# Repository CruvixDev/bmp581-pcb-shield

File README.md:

# BMP581 shield project (Kicad)

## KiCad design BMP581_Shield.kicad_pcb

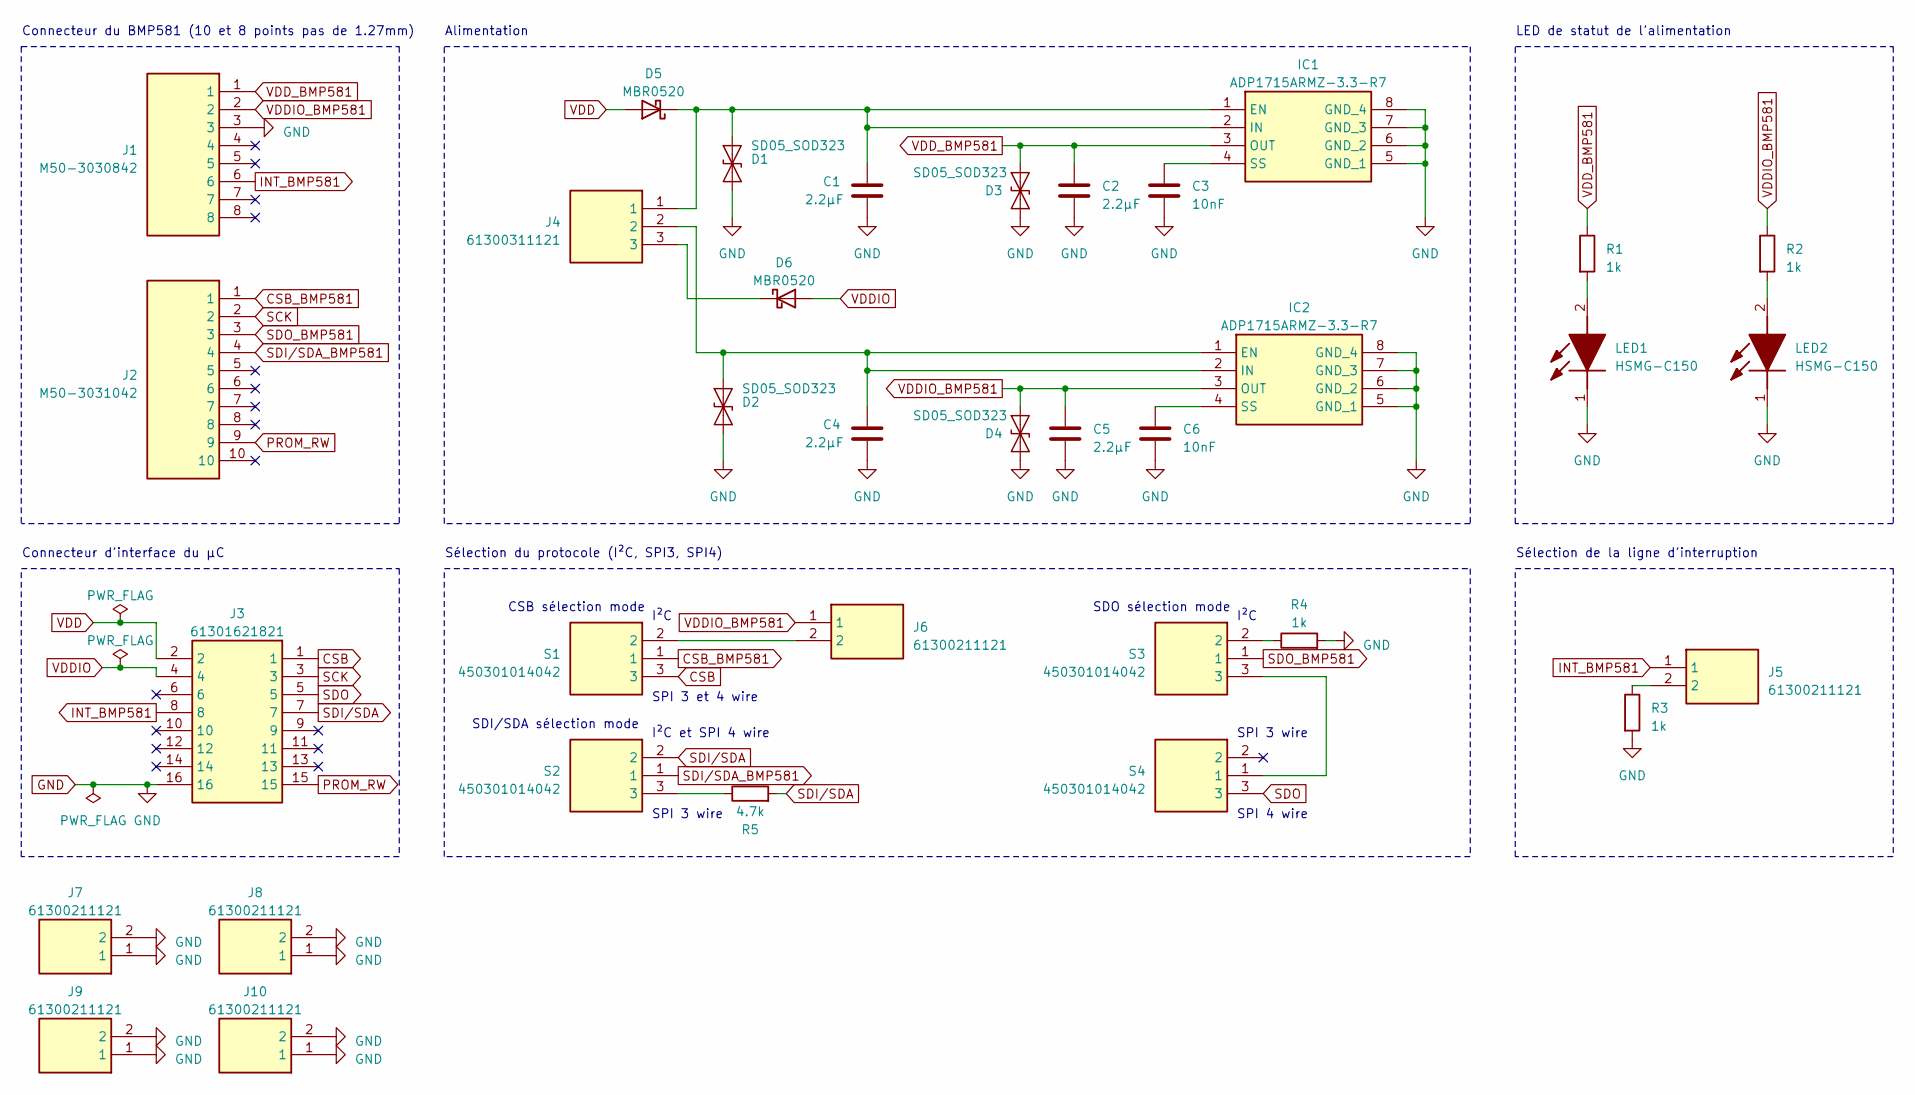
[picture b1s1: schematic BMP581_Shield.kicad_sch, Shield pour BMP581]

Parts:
C1, C2, C4, C5: 2.2µF; C_0603_1608Metric_Pad1.08x0.95mm_HandSolder
C3, C6: 10nF; C_0603_1608Metric_Pad1.08x0.95mm_HandSolder
D1, D2, D3, D4: SD05_SOD323; D_SOD-323_HandSoldering
D5, D6: MBR0520; D_SOD-123
IC1, IC2: ADP1715ARMZ-3.3-R7; SOP65P490X110-8N; Mouser Part Number 584-ADP1715ARMZ3.3R7
J1: M50-3030842; M503030842; Manufacturer_Part_Number M50-3030842; Mouser Part Number 855-M50-3030842
J2: M50-3031042; M503031042; Manufacturer_Part_Number M50-3031042; Mouser Part Number 855-M50-3031042
J3: 61301621821; RHDR16W79P254X254_2X8_2082X508X860P; Mouser Part Number 710-61301621821
J4: 61300311121; HDRV3W64P0X254_1X3_762X254X869P; Mouser Part Number 710-61300311121
J5, J6, J7, J8, J9, J10: 61300211121; HDRV2W110P0X254_1X2_508X254X854P; Mouser Part Number 710-61300211121
LED1, LED2: HSMG-C150; LEDC3216X120N; Mouser Part Number 630-HSMG-C150
R1, R2, R3, R4: 1k; R_0603_1608Metric_Pad0.98x0.95mm_HandSolder
R5: 4.7k; R_0603_1608Metric_Pad0.98x0.95mm_HandSolder
S1, S2, S3, S4: 450301014042; Mouser Part Number 710-450301014042

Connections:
CSB: J3.1, S1.3
CSB_BMP581: J2.1, S1.1
GND: C1.2, C2.2, C3.2, C4.2, C5.2, C6.2, D1.1 (A1), D2.1 (A1), D3.1 (A1), D4.1 (A1), IC1.5 (GND_1), IC1.6 (GND_2), IC1.7 (GND_3), IC1.8 (GND_4), IC2.5 (GND_1), IC2.6 (GND_2), IC2.7 (GND_3), IC2.8 (GND_4), J1.3, J3.16, J7.1, J7.2, J8.1, J8.2, J9.1, J9.2, J10.1, J10.2, LED1.1 (K), LED2.1 (K), R3.2, R4.2
INT_BMP581: J1.6, J3.8, J5.1
unnamed: C1.1, D1.2 (A2), D5.1 (K), IC1.1 (EN), IC1.2 (IN), J4.1
unnamed: C4.1, D2.2 (A2), IC2.1 (EN), IC2.2 (IN), J4.2
unnamed: D6.1 (K), J4.3
unnamed: C3.1, IC1.4 (SS)
unnamed: C6.1, IC2.4 (SS)
unnamed: J5.2, R3.1
unnamed: J6.2, S1.2
unnamed: LED1.2 (A), R1.2
unnamed: LED2.2 (A), R2.2
unnamed: R4.1, S3.2
unnamed: R5.1, S2.3
unnamed: S3.3, S4.1
PROM_RW: J2.9, J3.15
SCK: J2.2, J3.3
SDI/SDA: J3.7, R5.2, S2.2
SDI/SDA_BMP581: J2.4, S2.1
SDO: J3.5, S4.3
SDO_BMP581: J2.3, S3.1
VDD: D5.2 (A), J3.2
VDDIO: D6.2 (A), J3.4
VDDIO_BMP581: C5.1, D4.2 (A2), IC2.3 (OUT), J1.2, J6.1, R2.1
VDD_BMP581: C2.1, D3.2 (A2), IC1.3 (OUT), J1.1, R1.1

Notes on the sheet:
SPI 3 wire
I²C et SPI 4 wire
Alimentation
Connecteur d'interface du µC
LED de statut de l'alimentation
SPI 4 wire
SDI/SDA sélection mode
Connecteur du BMP581 (10 et 8 points pas de 1.27mm)
I²C
SPI 3 et 4 wire
CSB sélection mode
SDO sélection mode
Sélection du protocole (I²C, SPI3, SPI4)
Sélection de la ligne d'interruption

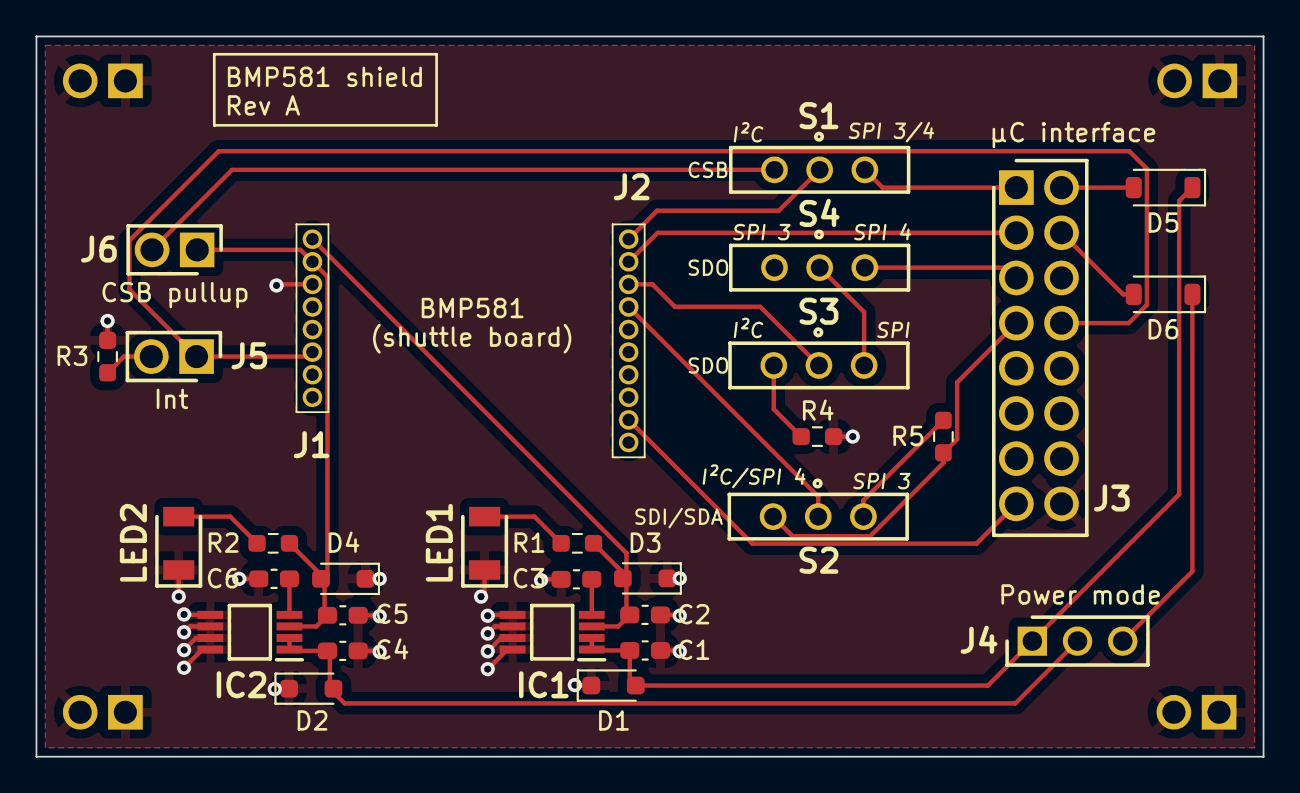
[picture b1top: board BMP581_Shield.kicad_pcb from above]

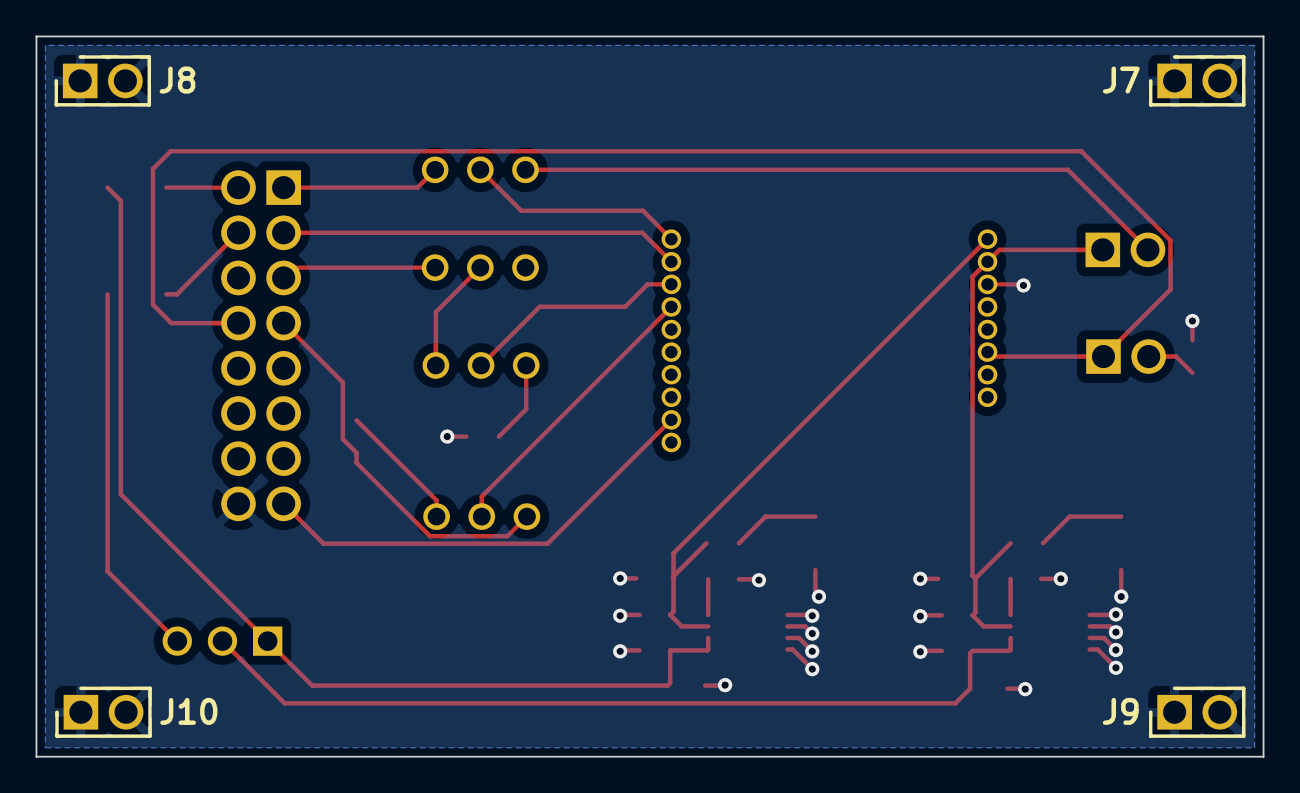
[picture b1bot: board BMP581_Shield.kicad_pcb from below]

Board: 2 copper layers, 69.0 x 40.5 mm, 35 parts (4 on the bottom side), 26 nets.
